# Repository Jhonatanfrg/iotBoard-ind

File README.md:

# iotBoard-ind
PCB and 3D Model of a board, for the IoT Hardware designe class
main: You can find the readme file.
master: you can find the PCB files and 3D model.

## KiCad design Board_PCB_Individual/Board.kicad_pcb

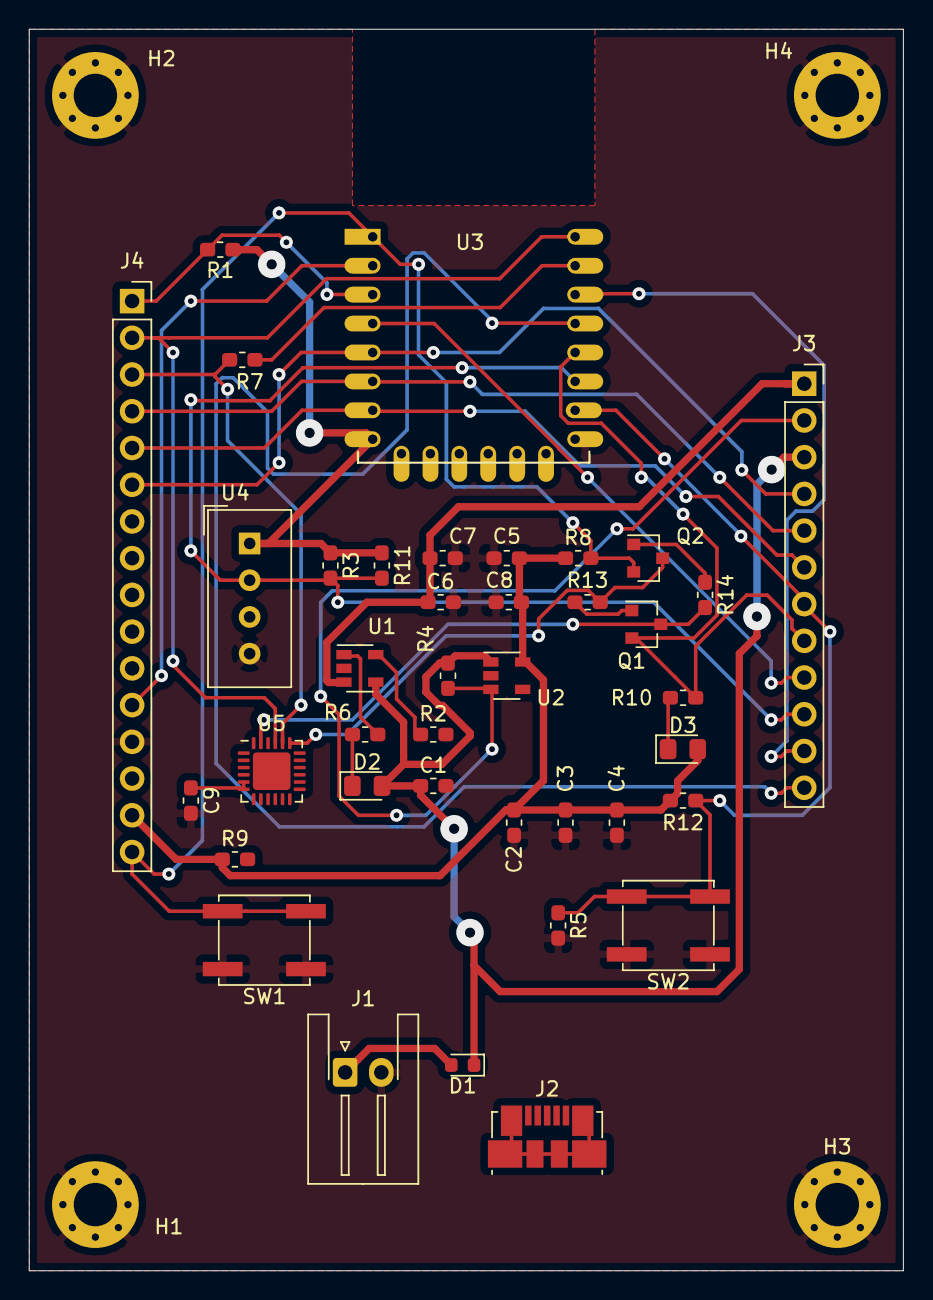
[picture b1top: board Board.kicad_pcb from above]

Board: 2 copper layers, 60.5 x 85.9 mm, 43 parts (0 on the bottom side), 32 nets.

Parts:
C1, C5, C7: 10u; C_0603_1608Metric_Pad1.05x0.95mm_HandSolder
C2: 10v; C_0603_1608Metric_Pad1.05x0.95mm_HandSolder
C3, C8: 100n; C_0603_1608Metric_Pad1.05x0.95mm_HandSolder
C4, C9: 1u; C_0603_1608Metric_Pad1.05x0.95mm_HandSolder
C6: 4.7u; C_0603_1608Metric_Pad1.05x0.95mm_HandSolder
D1: D_Schottky; D_0603_1608Metric
D2, D3: LED; LED_0805_2012Metric_Pad1.15x1.40mm_HandSolder
H1, H2, H3, H4: MountingHole_Pad; MountingHole_3mm_Pad_Via
J1: Conn_01x02; JST_XH_S2B-XH-A-1_1x02_P2.50mm_Horizontal
J2: USB_B_Micro; USB_Micro-B_Molex_47346-0001
J3: Conn_01x12; PinSocket_1x12_P2.54mm_Vertical
J4: Conn_01x16; PinSocket_1x16_P2.54mm_Vertical
Q1, Q2: Q_NPN_BCE; SOT-23
R1, R3, R4, R5, R8, R9, R12, R13, R14: 10k; R_0603_1608Metric_Pad1.05x0.95mm_HandSolder
R2: 2K; R_0603_1608Metric_Pad1.05x0.95mm_HandSolder
R6, R7, R10: 1k; R_0603_1608Metric_Pad1.05x0.95mm_HandSolder
R11: 4k7; R_0603_1608Metric_Pad1.05x0.95mm_HandSolder
SW1, SW2: SW_Push; SW_SPST_EVPBF
U1: MCP73831-2-OT; SOT-23-5
U2: AP2127K-3.3; SOT-23-5
U3: ESP-12F; ESP-12E
U4: DHT11; Aosong_DHT11_5.5x12.0_P2.54mm
U5: CP2102N-A01-GQFN24_C; QFN-24-1EP_4x4mm_P0.5mm_EP2.6x2.6mm

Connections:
+3V3: C2.1, C3.1, C4.1, C5.1, C8.1, D3.2, J4.15, R1.1, R3.1, R8.1, R9.1, R11.1, R12.1, U2.5, U3.8, U4.1
+BATT: C6.1, C7.1, D1.2, J1.1, J3.1, U1.3
ADC0: J4.12, U3.2
DTR: Q1.3, R14.2, U5.23
EN: J4.1, R1.2, U3.3
EN_REG: J3.2, R4.2, U2.3
GND: C1.2, C2.2, C3.2, C4.2, C5.2, C6.2, C7.2, C8.2, C9.2, H1.1, H2.1, H3.1, H4.1, J1.2, J2.5, J4.13, R2.2, R5.2, SW1.1, SW2.1, U1.2, U2.2, U3.9, U4.4, U5.2, U5.25
GPIO0: J3.8, Q1.2, R10.2, U3.12
GPIO2: J3.10, R3.2, R11.2, U3.11, U4.2
GPIO4_SDA: J3.12, U3.13
GPIO5_SCL: J3.11, U3.14
GPIO12_MISO: J3.5, J4.4, U3.6
GPIO13_MOSI: J3.6, J4.5, U3.7
GPIO14_SCK: J3.4, J4.6, U3.5
GPIO15: J3.7, R5.1, R12.2, SW2.2, U3.10
GPIO16: J3.9, U3.4
unnamed: C9.1, U5.5, U5.6
unnamed: D2.1, R6.1
unnamed: D3.1, R10.1
unnamed: J2.2, U5.4
unnamed: J2.3, U5.3
unnamed: Q1.1, R13.1
unnamed: Q2.1, R14.1
unnamed: R2.1, U1.5
unnamed: R7.2, U3.15
unnamed: R9.2, U5.9
RST: J4.16, Q2.2, R8.2, SW1.2, U3.1
RTS: Q2.3, R13.2, U5.19
RXD: J4.3, R7.1, U5.20
STAT: R6.2, U1.1
TXD: J4.2, U3.16, U5.21
VBUS: C1.1, D1.1, D2.2, J2.1, J3.3, R4.1, U1.4, U2.1, U5.7, U5.8

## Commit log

2020-12-07 Agregue archivos del PCB y el modelo 3D
2020-12-07 Agregue video con presentación del esquemático, PCB y modelo 3D
